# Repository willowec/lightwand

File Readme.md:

# Light Wand

A Persistance of Vision project for the University of Maine Electrical and Computer Engineering department.

## Compiling

1. Open a linux environment
2. Change directory to the directory of this Readme
3. Run the following commands:

        git submodule update --init --recursive
        mkdir build
        cd build
	    export PICO_SDK_PATH=/path/to/pico/pico-sdk
        cmake ..
        make

## Credits

 - Code, design, and documentation by Willow Cunningham unless otherwise specified
 - Project comissioned by Dr. Yifeng Zhu and advised by Professor Andrew Sheaff

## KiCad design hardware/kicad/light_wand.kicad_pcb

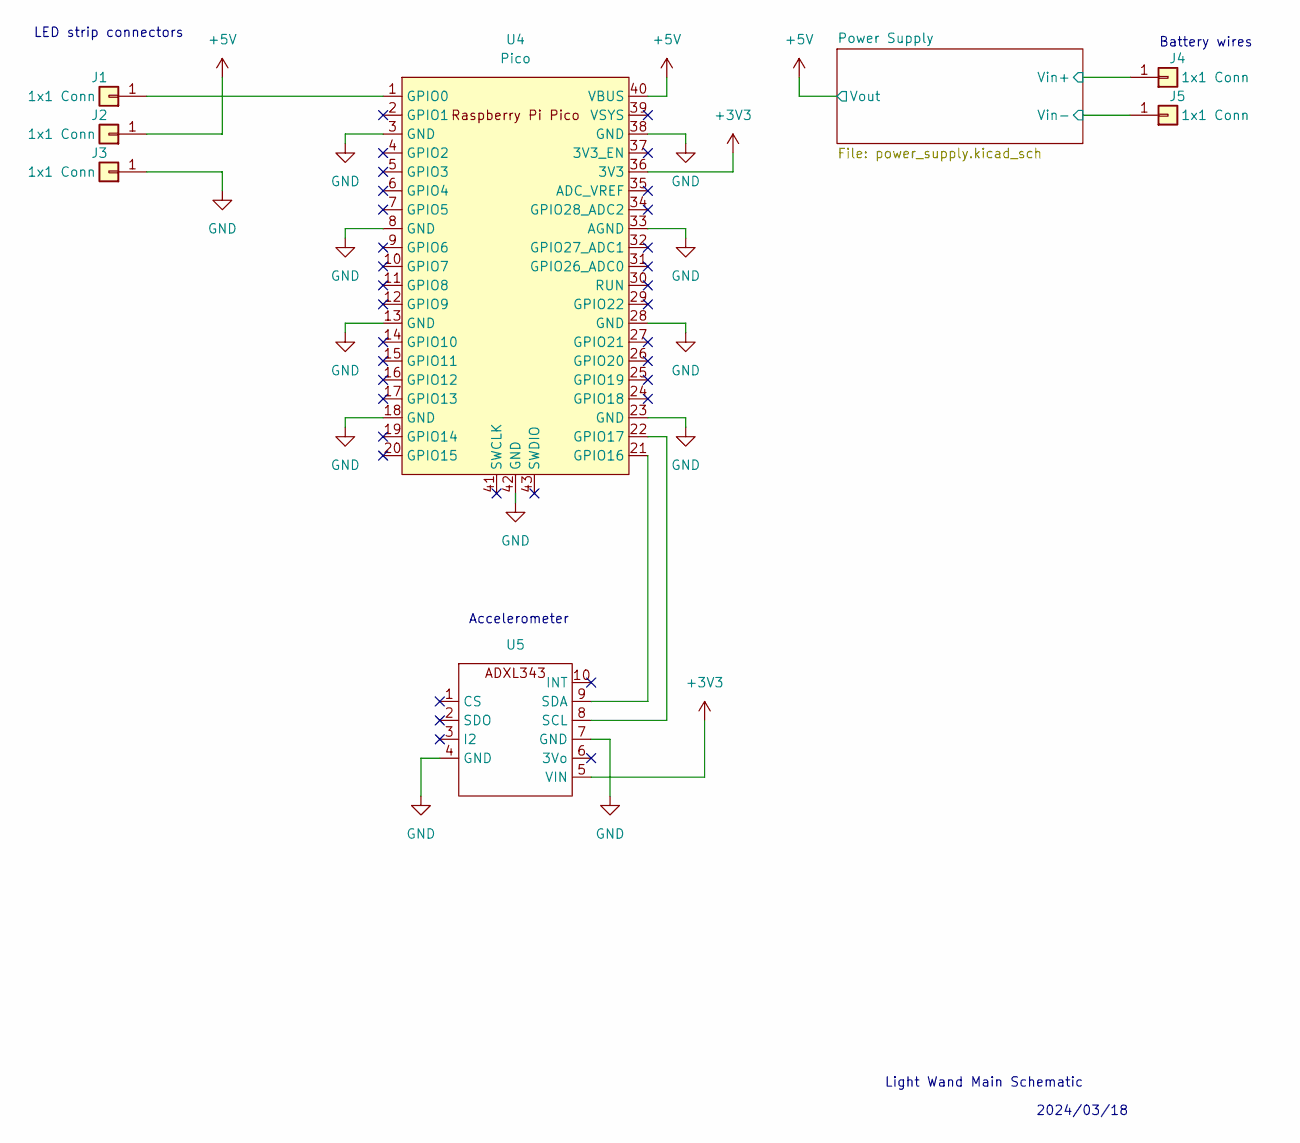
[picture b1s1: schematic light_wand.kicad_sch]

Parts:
J1, J2, J3, J4, J5: 1x1 Conn; SolderWire-0.5sqmm_1x01_D0.9mm_OD2.1mm
U4: Pico; RPi_Pico_SMD_TH
U5: ADXL343_Breakout_ThruHole

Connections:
+3V3: U4.36 (3V3), U5.5 (VIN)
+5V: J2.1, U4.40 (VBUS); also elsewhere on the board
/Power Supply/Vin+: J4.1; also elsewhere on the board
unnamed: J1.1, U4.1 (GPIO0)
unnamed: U4.21 (GPIO16), U5.9 (SDA)
unnamed: U4.22 (GPIO17), U5.8 (SCL)

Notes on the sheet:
LED strip connectors
Accelerometer
Battery wires
Light Wand Main Schematic
2024/03/18

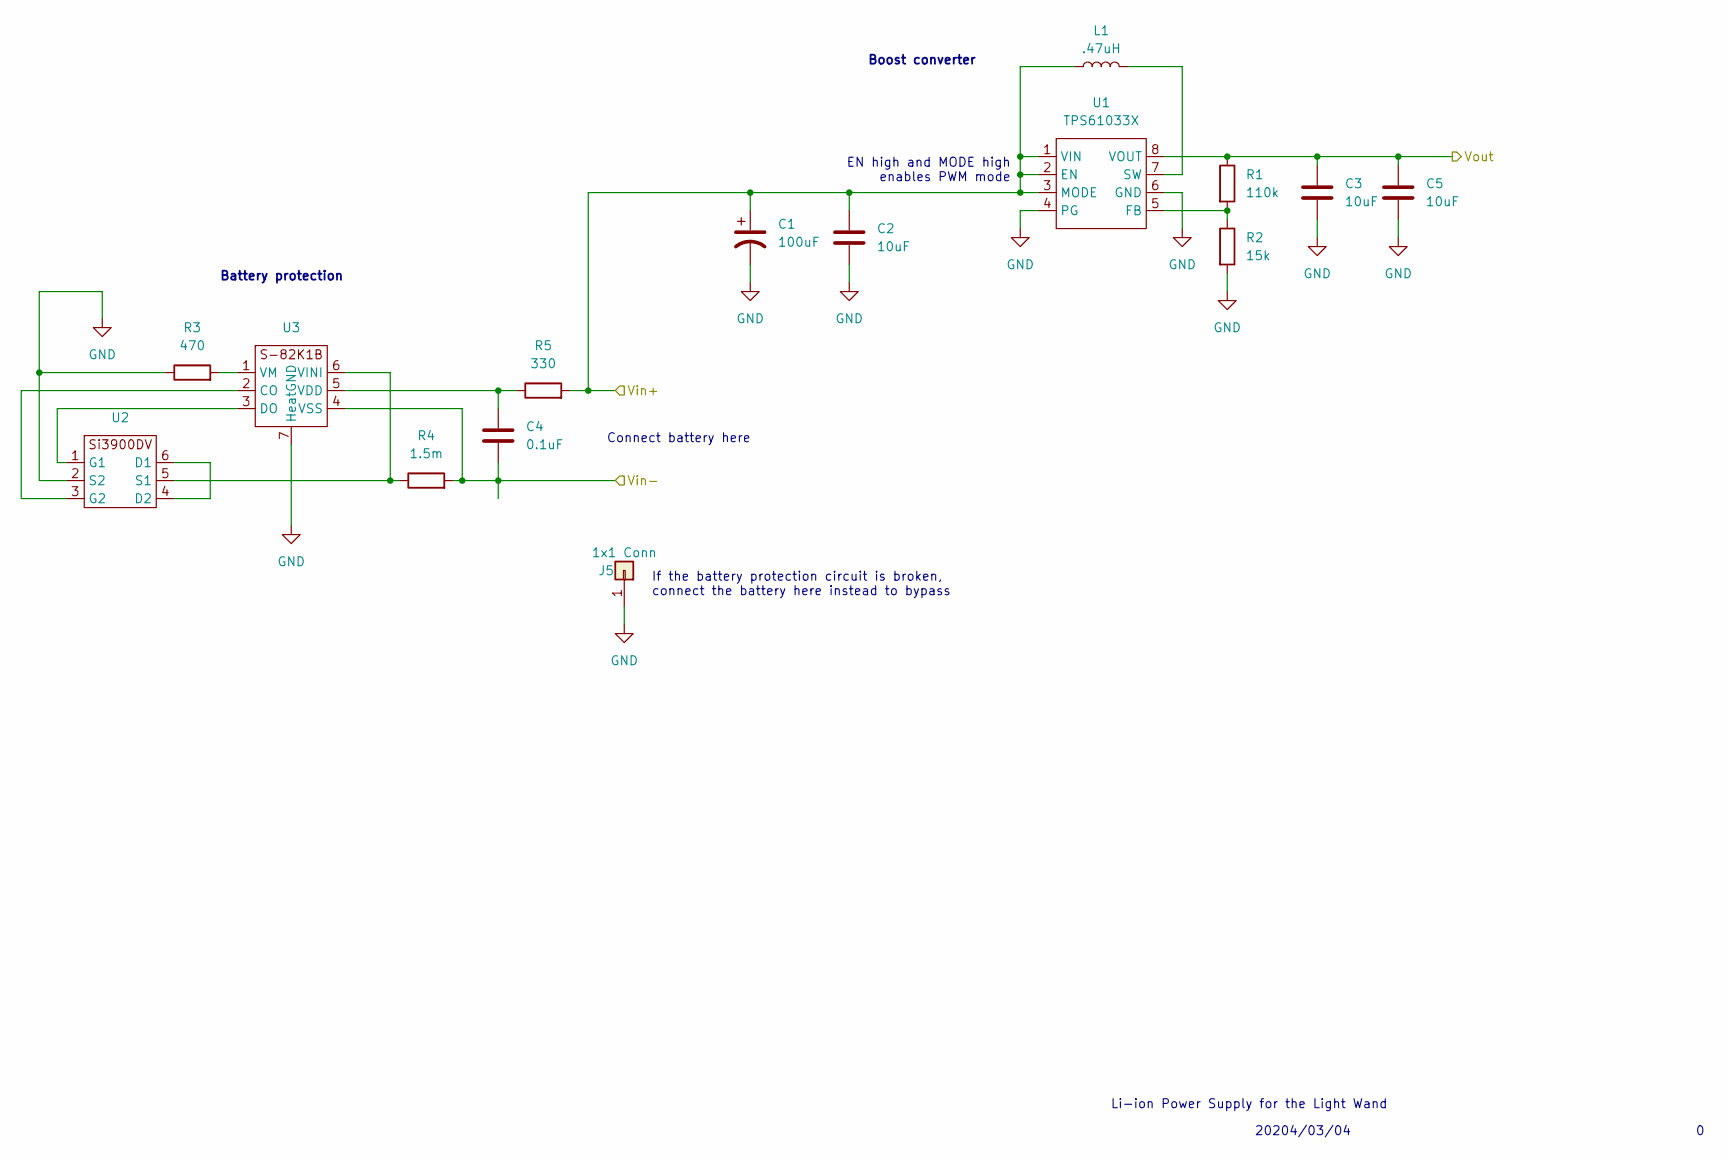
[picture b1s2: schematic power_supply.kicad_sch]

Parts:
C1: 100uF; CP_Radial_D5.0mm_P2.50mm
C2, C3, C5: 10uF; C_0603_1608Metric
C4: 0.1uF; C_0603_1608Metric
J5: 1x1 Conn; SolderWire-0.5sqmm_1x01_D0.9mm_OD2.1mm
L1: .47uH; Inductor_SMD_L_7.3x7.3_H3.5
R1: 110k; R_0603_1608Metric
R2: 15k; R_0603_1608Metric
R3: 470; R_0603_1608Metric
R4: 1.5m; R_2512_6332Metric
R5: 330; R_0603_1608Metric
U1: TPS61033X; SOT-583-8
U2: SOT-23-6_Handsoldering
U3: HSNT-6

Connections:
+5V: C3.1, C5.1, R1.1, U1.8 (VOUT); also elsewhere on the board
/Power Supply/Vin+: C1.1, C2.1, L1.1, R5.2, U1.1 (VIN), U1.2 (EN), U1.3 (MODE); also elsewhere on the board
unnamed: R1.2, R2.1, U1.5 (FB)
unnamed: L1.2, U1.7 (SW)
unnamed: U2.4 (D2), U2.6 (D1)
unnamed: U2.1 (G1), U3.3 (DO)
unnamed: U2.3 (G2), U3.2 (CO)
unnamed: R4.1, U2.5 (S1), U3.6 (VINI)
unnamed: C4.1, R5.1, U3.5 (VDD)
unnamed: R3.2, U3.1 (VM)

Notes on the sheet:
If the battery protection circuit is broken, connect the battery here instead to bypass
Boost converter
EN high and MODE high enables PWM mode
20204/03/04
Li-ion Power Supply for the Light Wand
Connect battery here
Battery protection

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
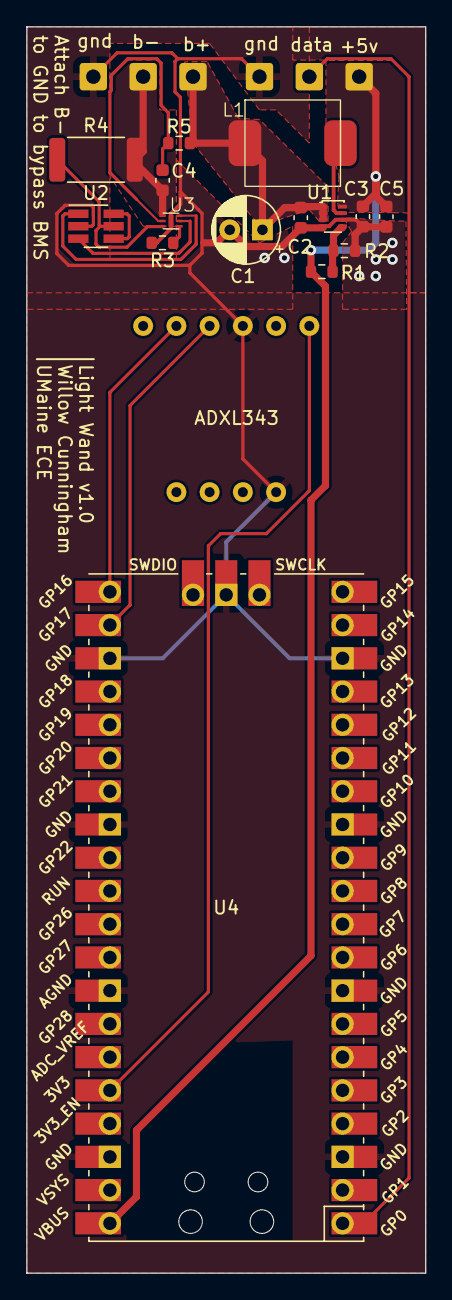
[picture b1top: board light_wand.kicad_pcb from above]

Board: 2 copper layers, 30.5 x 95.2 mm, 22 parts (0 on the bottom side), 16 nets.

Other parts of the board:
J6: 1x1 Conn; SolderWire-0.5sqmm_1x01_D0.9mm_OD2.1mm

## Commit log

2024-02-07 set up initial build
2024-02-07 Added ws2812 from the pico examples. Not sure if it works yet
2024-02-08 First neopixel in the chain functional
2024-02-08 Attempt to control full strip, sending green makes entire strip a faint white
2024-02-08 can now write one color to all 30 pixels at once!
2024-02-09 resolved error in the timings
2024-02-13 began acceleromter driver
2024-02-13 reading over i2c is currently unsuccessful
2024-02-14 dumb mistake of out of order function arguments cost me 40 minutes
2024-02-15 Now printing 3axis motion
2024-02-17 accelleration channels mapped to color channels
2024-02-17 Figured out 16G range is necessary for ADX
2024-02-17 added note about 8g
2024-02-18 Selected components for the power supply
2024-02-20 minor link edits
2024-02-20 I clearly need to do some research into how thes accelerometer algorithms work
2024-02-21 Began working on a transform module
2024-02-21 Attempt at full transform seems to have failed
2024-02-21 moved transform to a branch and began working on magnitude
2024-02-22 Attempted a magnitude based 1d position system with better but still bad results
2024-02-27 implemented simple system that only knows what direction the wand is being waved in
2024-02-29 Created script that generates the h file for the alphabet
2024-03-01 defined message
2024-03-01 Added function to turn on and off individual pixels in wand
2024-03-01 Char displaying is currently not quite working
2024-03-01 plan made to reduce size of wand to 15 pixels
2024-03-05 Ignoring most kicad files
2024-03-05 Finished boost converter schematic, need to add battery protection
2024-03-06 got backup adx working
2024-03-06 moved to generating alphabet from font and generated 15 pixel font
2024-03-08 Tested boost converter
2024-03-08 increased turn detection MSS to 40ms^2, granting much better direction detection
2024-03-08 misc adjustments
2024-03-08 Added note about fiberglass wand implementation
2024-03-14 Finished schematic layout for power supply
2024-03-16 Added footprint for battery prot ic
2024-03-16 Finished footprints for all ICs
2024-03-18 Added pico to the schematic
2024-03-18 Updated submdule to allow building on my laptop
2024-03-20 Tested boost converter with dissapointing results
2024-03-21 Finished component selection for the boost conv
2024-03-21 Layed out schematic of the new boost converter design
2024-03-22 Added footprints to everything in the power supply
2024-03-22 Completed circuit schematic
2024-03-22 Began laying out the PCB
2024-03-25 Finished PCB layout
2024-03-26 Finished BOM and unit price calculation
2024-03-27 adjusted timings
2024-03-27 Added jerk calculation
2024-03-27 Moved direction calculations to be based on jerk
2024-03-27 Added moving average to Jerk
2024-03-27 Jerk experiments are not yeilding results
2024-03-27 Reverted to pre-jerk version for demo
2024-03-28 Finished planning for new boost converter ckt
2024-03-28 Re-did schematic for new boost converter
2024-03-28 Pre updated PCB layout
2024-03-28 Moved new components onto PCB
2024-03-28 Completed PCB laout
2024-03-28 Updated credits
2024-03-28 generated gerbers
2024-04-01 reorganized hardware directory
2024-04-01 Began build target + script for plotting accel data
2024-04-01 Demonstrated that averaging windows do not help the jerk
2024-04-01 fixed issue with jerk calculation
2024-04-01 Using hysteresis, implied direction is now nearly flawless in calculation
2024-04-02 Demonstrated how hysteresis fixes most of the jerk problems
2024-04-02 Implemented hysteresis based jerk direction calculations on the microcontroller
2024-04-03 Mostly finished with core1 code, however loop does not seem to be entered
2024-04-03 Fully implemented new rendering system, though there are honestly no discernable improvements
2024-04-04 Characterized column rendering - slower swings are actually better for rendering
2024-04-07 Began planning 3D prints for wand
2024-04-08 cleaned up hardware directory
2024-04-08 Chamfered edges to make the platform arms stronger
2024-04-09 Added screw holes to pcb mount
2024-04-09 initial pcb arms
2024-04-09 Completed initial test print for pcb holder
2024-04-10 Got the wand working with RGBW leds
2024-04-12 checkpoint for cad
2024-04-12 Modified pcb holder to have wider arms on the pico side
2024-04-14 Finished first draft of the handle 3D model
2024-04-16 Widened the switch port diameter by 2mm
2024-04-18 Widened dowel shaft and added screw guides
2024-04-24 increased height of pcb clamps by 0.2mm from 1.6mm to 1.8mm
2024-04-24 reduced dowel shaft width by 1mm
2024-04-25 Updated accelerometer axis to reflect pcb
2024-04-25 updated compilation instructions
2024-04-29 Updated rendering to have on pixels a white-blue and off pixels clear. Wand is now legible
2024-04-30 Added display state code
2024-05-01 Added a random color mode so that the wand can be useful even if it cant be waved
2024-05-01 regenerated alphabet to use bold font, resulting in a much clearer image
2024-05-01 Added a bit about future work
2024-08-13 Added notebook disclaimer
